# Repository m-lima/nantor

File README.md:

# Nantor

A wireless 42-key split keyboard made for Kailh Choc switches.

**Features**

- Flippable design
- [PillBug] support
- [BlackPill] support
- Wired and wireless support
- Battery power support
- Hotswap switches support

## Hardware

The board was designed with [KiCad] and can be found in [board/kicad](board/kicad).

The gerber files can be found in [board/kicad/gerber](board/kicad/gerber).

## ZMK

For wireless and wired mode. This firmware assumes that [PillBug] is being used.

> [!TIP]
>
> This is the latest and recommended configuration.

### Layout

> [!NOTE]
>
> Definition available at [zmk/shared/config/boards/shields/nantor/nantor.keymap](zmk/shared/config/boards/shields/nantor/nantor.keymap)

#### Base (colemak)

```
            ╭───╮                     ╭───╮
        ╭───┤ F ├───┬───╮     ╭───┬───┤ U ├───╮
    ╭───┤ W ├───┤ P │ B │     │ J │ L ├───┤ Y ├───╮
╭───┤ Q ├───┤ S ├───┼───┤     ├───┼───┤ E ├───┤ ; ├───╮
│Esc├───┤ R ├───┤ T │ G │     │ M │ N ├───┤ I ├───┤ ' │
├───┤ A ├───┤ C ├───┼───┤     ├───┼───┤ , ├───┤ O ├───┤
│Alt├───┤ X ├───┤ D │ V │     │ K │ H ├───┤ . ├───┤ \ │
╰───┤ Z ├───┘   ╰───┴───╯     ╰───┴───╯   ╰───┤ / ├───╯
    ╰───╯     ╭───┬───╮         ╭───┬───╮     ╰───╯
          ╭───┤Spc│Sft├───╮ ╭───┤NUM│Ent├───╮
          │Bsp├───┴───┤ ⌘ │ │Ctl├───┴───┤FNS│
          ╰───╯       ╰───╯ ╰───╯       ╰───╯
```

#### Base (qwerty)

```
            ╭───╮                     ╭───╮
        ╭───┤ E ├───┬───╮     ╭───┬───┤ I ├───╮
    ╭───┤ W ├───┤ R │ T │     │ Y │ U ├───┤ O ├───╮
╭───┤ Q ├───┤ D ├───┼───┤     ├───┼───┤ K ├───┤ P ├───╮
│Esc├───┤ S ├───┤ F │ G │     │ H │ J ├───┤ L ├───┤ ' │
├───┤ A ├───┤ C ├───┼───┤     ├───┼───┤ , ├───┤ ; ├───┤
│Alt├───┤ X ├───┤ V │ B │     │ N │ M ├───┤ . ├───┤ \ │
╰───┤ Z ├───┘   ╰───┴───╯     ╰───┴───╯   ╰───┤ / ├───╯
    ╰───╯     ╭───┬───╮         ╭───┬───╮     ╰───╯
          ╭───┤Spc│Sft├───╮ ╭───┤NUM│Ent├───╮
          │Bsp├───┴───┤ ⌘ │ │Ctl├───┴───┤FNS│
          ╰───╯       ╰───╯ ╰───╯       ╰───╯
```

#### Numbers

```
            ╭───╮                     ╭───╮
        ╭───┤ 8 ├───┬───╮     ╭───┬───┤PUp├───╮
    ╭───┤ 7 ├───┤ 9 │ 0 │     │Hom│PDn├───┤End├───╮
╭───┤ = ├───┤ 5 ├───┼───┤     ├───┼───┤ ↑ ├───┤Sft├───╮
│Esc├───┤ 4 ├───┤ 6 │ [ │     │ ← │ ↓ ├───┤ → ├───┤Ctl│
├───┤ - ├───┤ 2 ├───┼───┤     ├───┼───┤ , ├───┤ ⌘ ├───┤
│Alt├───┤ 1 ├───┤ 3 │ ] │     │Del│Tab├───┤ . ├───┤Alt│
╰───┤ ` ├───┘   ╰───┴───╯     ╰───┴───╯   ╰───┤ / ├───╯
    ╰───╯     ╭───┬───╮         ╭───┬───╮     ╰───╯
          ╭───┤Spc│Sft├───╮ ╭───┤ ∆ │Ent├───╮
          │Bsp├───┴───┤ ⌘ │ │Ctl├───┴───┤CFG│
          ╰───╯       ╰───╯ ╰───╯       ╰───╯
```

#### Functions

```
            ╭───╮                     ╭───╮
        ╭───┤F10├───┬───╮     ╭───┬───┤+B ├───╮
    ╭───┤ F9├───┤F11│F12│     │   │-B ├───┤   ├───╮
╭───┤Ins├───┤ F6├───┼───┤     ├───┼───┤ ‖ ├───┤Sft├───╮
│Esc├───┤ F5├───┤ F7│ F8│     │   │ ◄ ├───┤ ► ├───┤Ctl│
├───┤Cap├───┤ F2├───┼───┤     ├───┼───┤ V0├───┤ ⌘ ├───┤
│Alt├───┤ F1├───┤ F3│ F4│     │   │-V ├───┤+V ├───┤Alt│
╰───┤PSc├───┘   ╰───┴───╯     ╰───┴───╯   ╰───┤   ├───╯
    ╰───╯     ╭───┬───╮         ╭───┬───╮     ╰───╯
          ╭───┤Spc│Sft├───╮ ╭───┤CFG│Ent├───╮
          │Bsp├───┴───┤ ⌘ │ │Ctl├───┴───┤ ∆ │
          ╰───╯       ╰───╯ ╰───╯       ╰───╯
```

#### Config

```
            ╭───╮                     ╭───╮
        ╭───┤   ├───┬───╮     ╭───┬───┤   ├───╮
    ╭───┤   ├───┤   │BTC│     │   │   ├───┤   ├───╮
╭───┤   ├───┤BT4├───┼───┤     ├───┼───┤   ├───┤   ├───╮
│   ├───┤BT3├───┤   │   │     │   │   ├───┤   ├───┤CLM│
├───┤BLE├───┤BT1├───┼───┤     ├───┼───┤   ├───┤   ├───┤
│   ├───┤BT0├───┤BT2│   │     │   │   ├───┤   ├───┤QWT│
╰───┤USB├───┘   ╰───┴───╯     ╰───┴───╯   ╰───┤   ├───╯
    ╰───╯     ╭───┬───╮         ╭───┬───╮     ╰───╯
          ╭───┤   │   ├───╮ ╭───┤ ∆ │ ᛒ ├───╮
          │   ├───┴───┤   │ │ ⌁ ├───┴───┤ ∆ │
          ╰───╯       ╰───╯ ╰───╯       ╰───╯
```

### LED encoding

> [!NOTE]
>
> This is assuming that the board being used is the PillBug (nRF52840)

> [!NOTE]
>
> In this section, a low frequency means a 500ms period, while high frequency means a 250ms period

#### Battery

If no charge is detected, all LEDs will blink at a low frequency.
Similarly, when at 100% charge, all LEDs will blink at a high frequency.
For all other values, the LEDs will encode the charge as such:

| Charge | Bottom | Center | Top  |
| ------ | ------ | ------ | ---- |
| None   | Low    | Low    | Low  |
| < 10%  | Low    | Off    | Off  |
| < 20%  | High   | Off    | Off  |
| < 30%  | Full   | Off    | Off  |
| < 40%  | Full   | Low    | Off  |
| < 50%  | Full   | High   | Off  |
| < 60%  | Full   | Full   | Off  |
| < 70%  | Full   | Full   | Low  |
| < 80%  | Full   | Full   | High |
| < 90%  | Full   | Full   | Full |
| > 90%  | High   | High   | High |

#### Bluetooth

The left side LEDs will encode the currently active channel in binary with the bottom LED being the least significant bit.
For a stable connection, the LEDs will stay fully on.
When open for connections, they will blink at a high frequency.
Lastly, when disconnected, they will blink at a low frequency.

### Flashing

> [!NOTE]
>
> This is assuming that the board being used is the PillBug (nRF52840)

1. [Build the images](#build-the-images)
2. [Enter UF2 mode](#enter-uf2-mode)
3. [Load the images](#load-the-images)

#### Build the images

```bash
$ ./zmk/build.sh make p
```

> [!NOTE]
>
> The above command will do a pristine build. Check [zmk/build.sh](zmk/build.sh) for more options.

The output files will be located at `zmk/shared/build/(left|right)/zephyr/zmk.uf2`.

#### Enter UF2 mode

1. Connect the USB cable
2. Reset twice. To reset, either press the reset button or pull the `RST` pin down to `GND`
3. The board should show up as a storage device

#### Load the images

The board should be available as a USB storage device. Copy the `zmk/shared/build/(left|right)/zephyr/zmk.uf2` files to this new device. It should flash and reset automatically.

## QMK

For wired mode. This firmware assumes that [BlackPill] is being used.

> [!WARNING]
>
> This is the first version of **Nantor** and is no longer actively maintained.

[PillBug]: https://mechwild.com/product/pillbug
[BlackPill]: https://stm32-base.org/boards/STM32F103C8T6-Black-Pill.html
[KiCad]: https://www.kicad.org

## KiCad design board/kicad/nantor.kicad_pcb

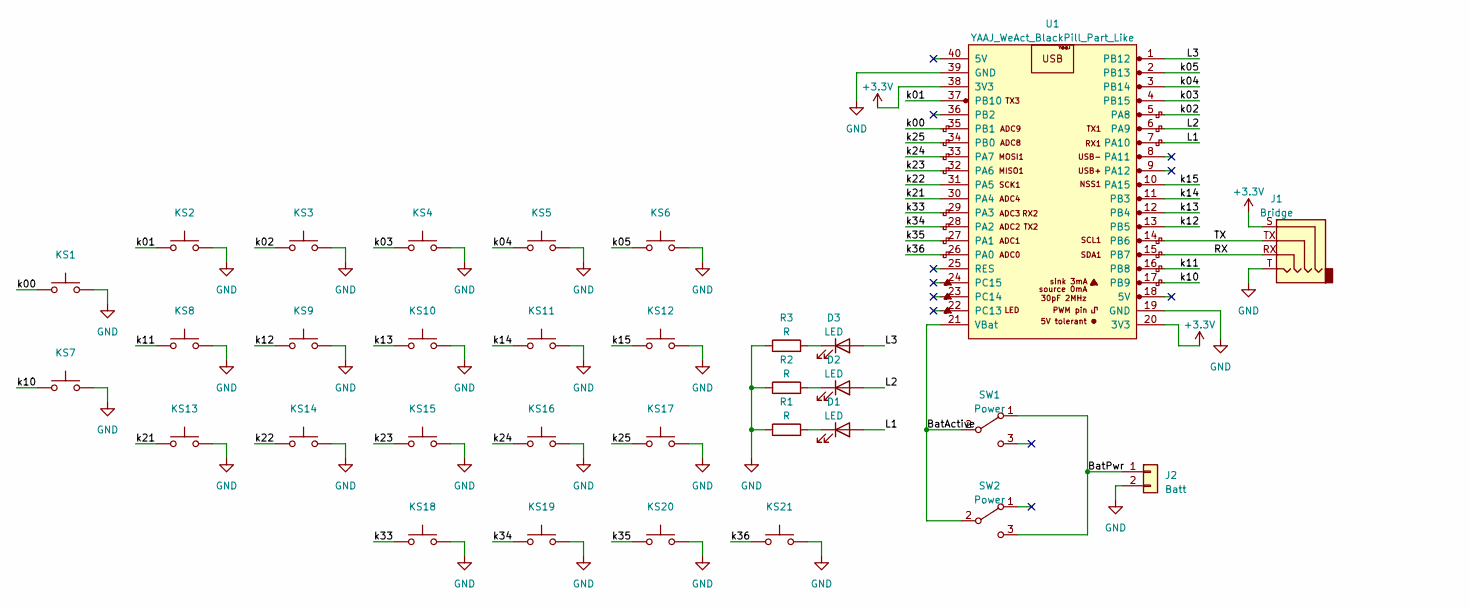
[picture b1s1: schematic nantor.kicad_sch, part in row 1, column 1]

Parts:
D1, D2, D3: LED; LED_0805
J1: Bridge; TRRS-PJ-320A
J2: Batt; JST_EH_S2B-EH_1x02_P2.50mm_Horizontal
KS1, KS2, KS3, KS4, KS5, KS6, KS7, KS8, KS9, KS10, KS11, KS12, KS13, KS14, KS15, KS16, KS17, KS18, KS19, KS20, KS21: Kailh_socket_PG1350_optional_reversible_clean
R1, R2, R3: R; LED_0805
SW1, SW2: Power; SW_SPDT_PCM12
U1: YAAJ_WeAct_BlackPill_Part_Like; BlackPill

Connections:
+3.3V: J1.S, U1.20 (3V3), U1.38 (3V3)
/BatActive: SW1.2 (B), SW2.2 (B), U1.21 (VBat)
/BatPwr: J2.1, SW1.1 (A), SW2.3 (C)
/L1: D1.2 (A), U1.7 (PA10)
/L2: D2.2 (A), U1.6 (PA9)
/L3: D3.2 (A), U1.1 (PB12)
/RX: J1.RX, U1.15 (PB7)
/TX: J1.TX, U1.14 (PB6)
/k00: KS1.1, U1.35 (PB1)
/k01: KS2.1, U1.37 (PB10)
/k02: KS3.1, U1.5 (PA8)
/k03: KS4.1, U1.4 (PB15)
/k04: KS5.1, U1.3 (PB14)
/k05: KS6.1, U1.2 (PB13)
/k10: KS7.1, U1.17 (PB9)
/k11: KS8.1, U1.16 (PB8)
/k12: KS9.1, U1.13 (PB5)
/k13: KS10.1, U1.12 (PB4)
/k14: KS11.1, U1.11 (PB3)
/k15: KS12.1, U1.10 (PA15)
/k21: KS13.1, U1.30 (PA4)
/k22: KS14.1, U1.31 (PA5)
/k23: KS15.1, U1.32 (PA6)
/k24: KS16.1, U1.33 (PA7)
/k25: KS17.1, U1.34 (PB0)
/k33: KS18.1, U1.29 (PA3)
/k34: KS19.1, U1.28 (PA2)
/k35: KS20.1, U1.27 (PA1)
/k36: KS21.1, U1.26 (PA0)
GND: J1.T, J2.2, KS1.2, KS2.2, KS3.2, KS4.2, KS5.2, KS6.2, KS7.2, KS8.2, KS9.2, KS10.2, KS11.2, KS12.2, KS13.2, KS14.2, KS15.2, KS16.2, KS17.2, KS18.2, KS19.2, KS20.2, KS21.2, R1.1, R2.1, R3.1, U1.19 (GND), U1.39 (GND)
unnamed: D1.1 (K), R1.2
unnamed: D2.1 (K), R2.2
unnamed: D3.1 (K), R3.2

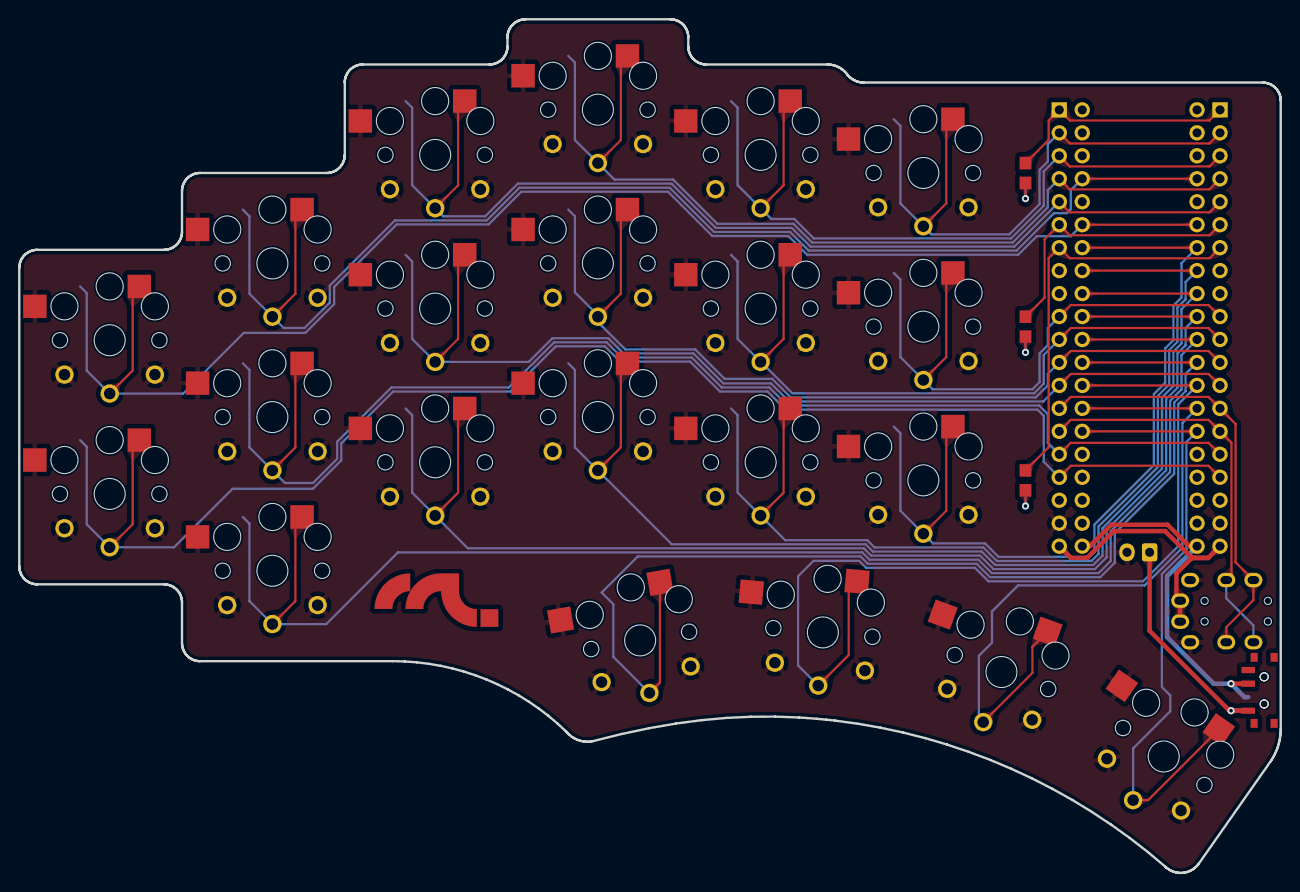
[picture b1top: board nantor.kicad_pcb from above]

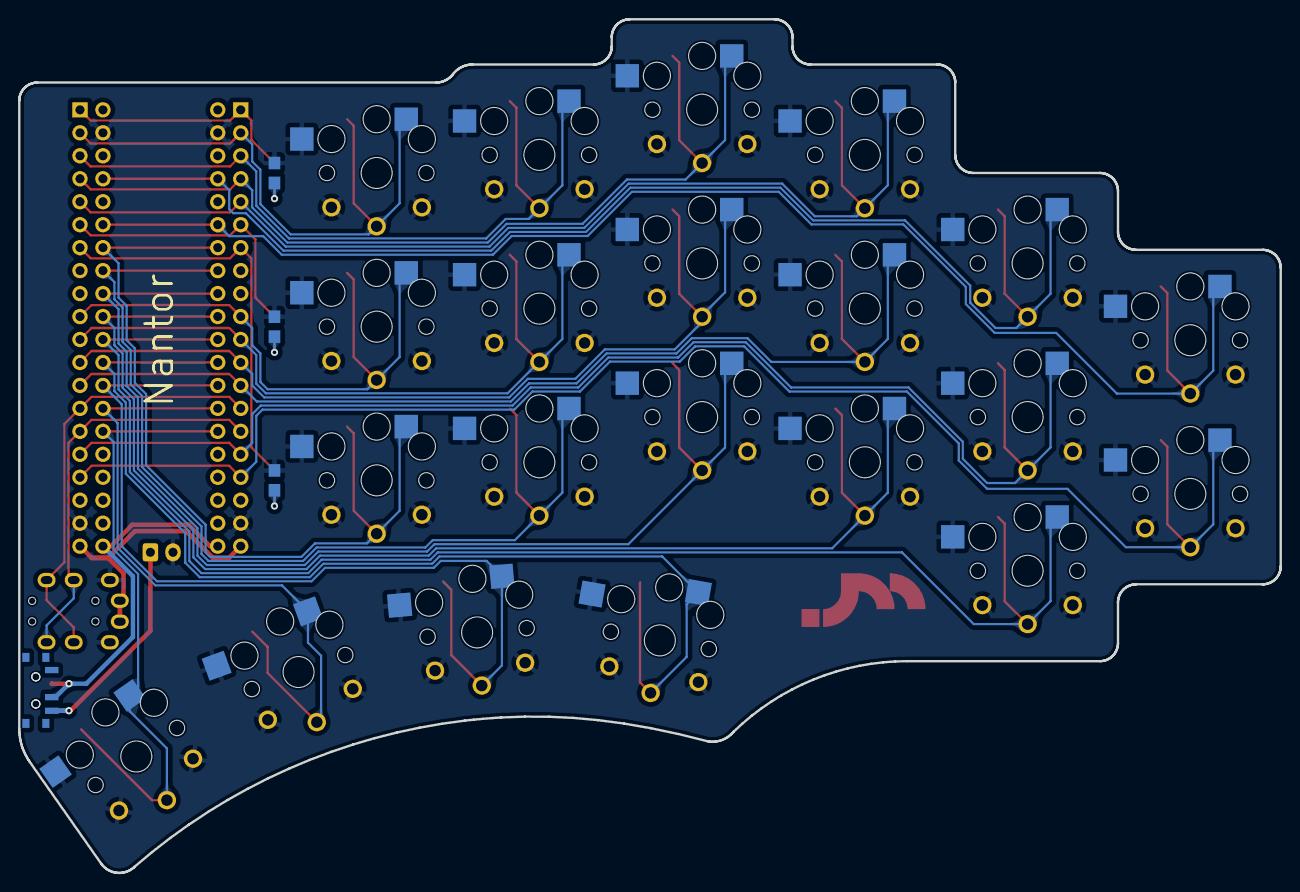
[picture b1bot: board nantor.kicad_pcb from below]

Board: 2 copper layers, 139.5 x 94.4 mm, 32 parts (5 on the bottom side), 33 nets.

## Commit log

2024-01-19 Add qmk stuffs
2024-01-19 Add zmk stuff
2024-01-19 Bring in QMK
2024-01-19 Add BT controls
2024-01-19 Untrack backups
2024-01-19 Remove cache
2024-06-07 Only update zmk submodule
2024-06-07 Detect yarn initialization
2024-06-07 Expose `,` to the `number` layer
2024-06-07 Add readme
2024-06-07 Add image
2024-08-15 Add base for 3d printing
2024-08-16 Update to use parametric offset
2024-08-16 Check that matches pcb
2024-08-17 Add board pdf
2024-08-17 Update case base
2024-08-17 Add blender files
2024-08-20 Update designs
2024-08-20 Add freeCAD
2024-08-20 Add stls
2024-08-24 Revamp case design
    Based on the first print, modifications to accommodate tolerances and
    get ready for screws
2024-08-24 Include schematics
2024-08-25 Clean up freecad dir
2024-08-25 Add new simpler version
2024-08-25 Move the right side to where freecad expects it
2024-08-25 Make simpler case with no top
2024-08-26 Rename to keep the same pattern
2024-08-26 Fix the offset of the inner bound
2024-08-26 Fix offsets and use hairline
2024-08-29 Include picture
2024-08-29 Reorg case vs board
2024-09-16 Update build script
2025-04-04 Make switch open
2025-04-04 Update outputs
2025-08-29 Add to-do's
2025-08-29 Add fusion stuff
2025-08-29 Remove silkscreens
2025-08-29 Move battery connector
2025-08-29 Add LEDs
2025-08-29 Start nixifying
2025-09-10 Reduce amount of vias
2025-09-10 Add keycap boundary
2025-09-10 Flatten keymap file
2025-09-10 Increase ground plane
2025-09-10 Rename layer
2025-09-10 Update keymap: remove trans
2025-09-10 Update TODO
2025-09-10 Add references
2025-09-10 All should be a success flow
2025-09-10 Nixify zmk.. sorta..
2025-09-10 Update zmk
2025-09-10 Fixup devcontainer
2025-09-10 Have pre-built behaviors
2025-09-10 Move module
2025-09-10 Start module
2025-09-10 Scaffold usage of new module
2025-09-10 WIP: Work towards something that compiles
2025-09-10 Update devcontainer; Update README/TODO
2025-09-11 Fix device tree source
2025-09-11 Update references
2025-09-11 Tighten the keyboard layout
2025-09-12 Update parameter names
2025-09-12 Improve (slightly) the devcontainer
2025-09-12 Experiment with a new, direct, builder script
2025-09-13 Improve build script
2025-09-13 Start using events and message queues
2025-09-22 Allow using podman
2025-09-22 Building
2025-09-22 WIP: Reset me
2025-09-26 Fix nix for zmk (using podman)
2025-09-26 A very simple version working
2025-09-26 Print new version
2025-09-27 First prototype to upload
2025-09-27 Blink on startup
2025-09-27 Update pins to match the board
2025-09-27 Experiment with logging
2025-09-28 Fix behavior
2025-09-28 Implement key rollover
2025-09-29 Dont quote the pod var
2025-10-30 Explain LEDs
2025-11-14 Add resetter command
2025-11-14 Make blinks more discernable
